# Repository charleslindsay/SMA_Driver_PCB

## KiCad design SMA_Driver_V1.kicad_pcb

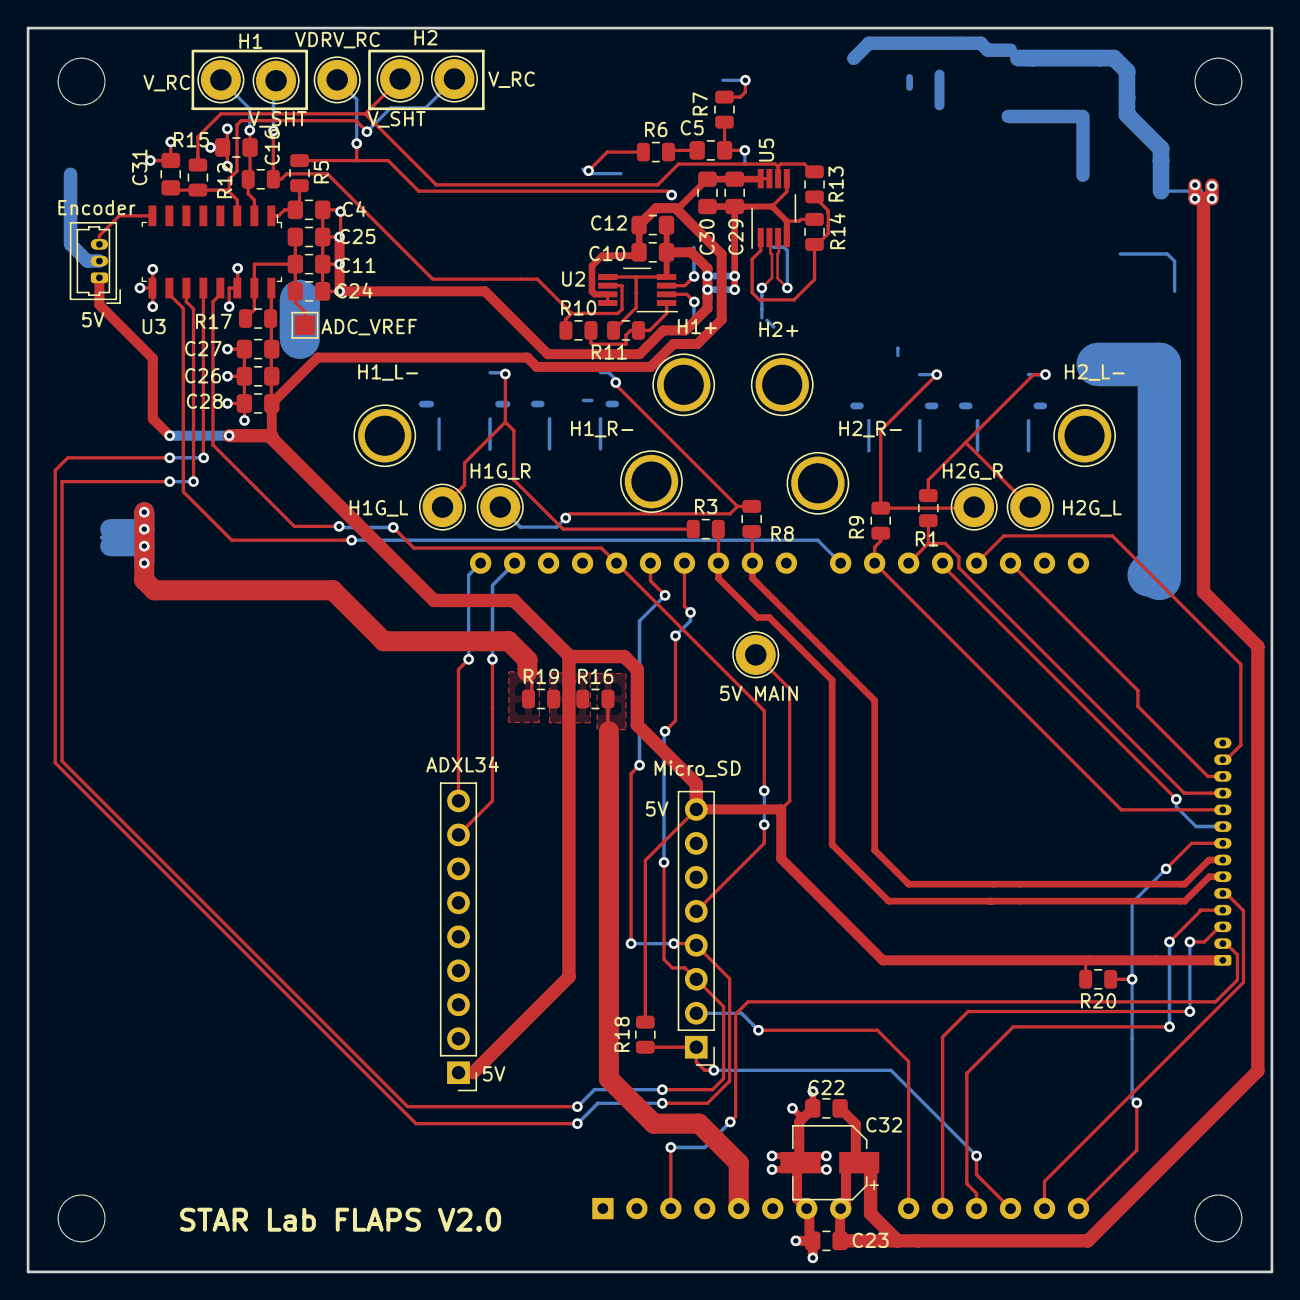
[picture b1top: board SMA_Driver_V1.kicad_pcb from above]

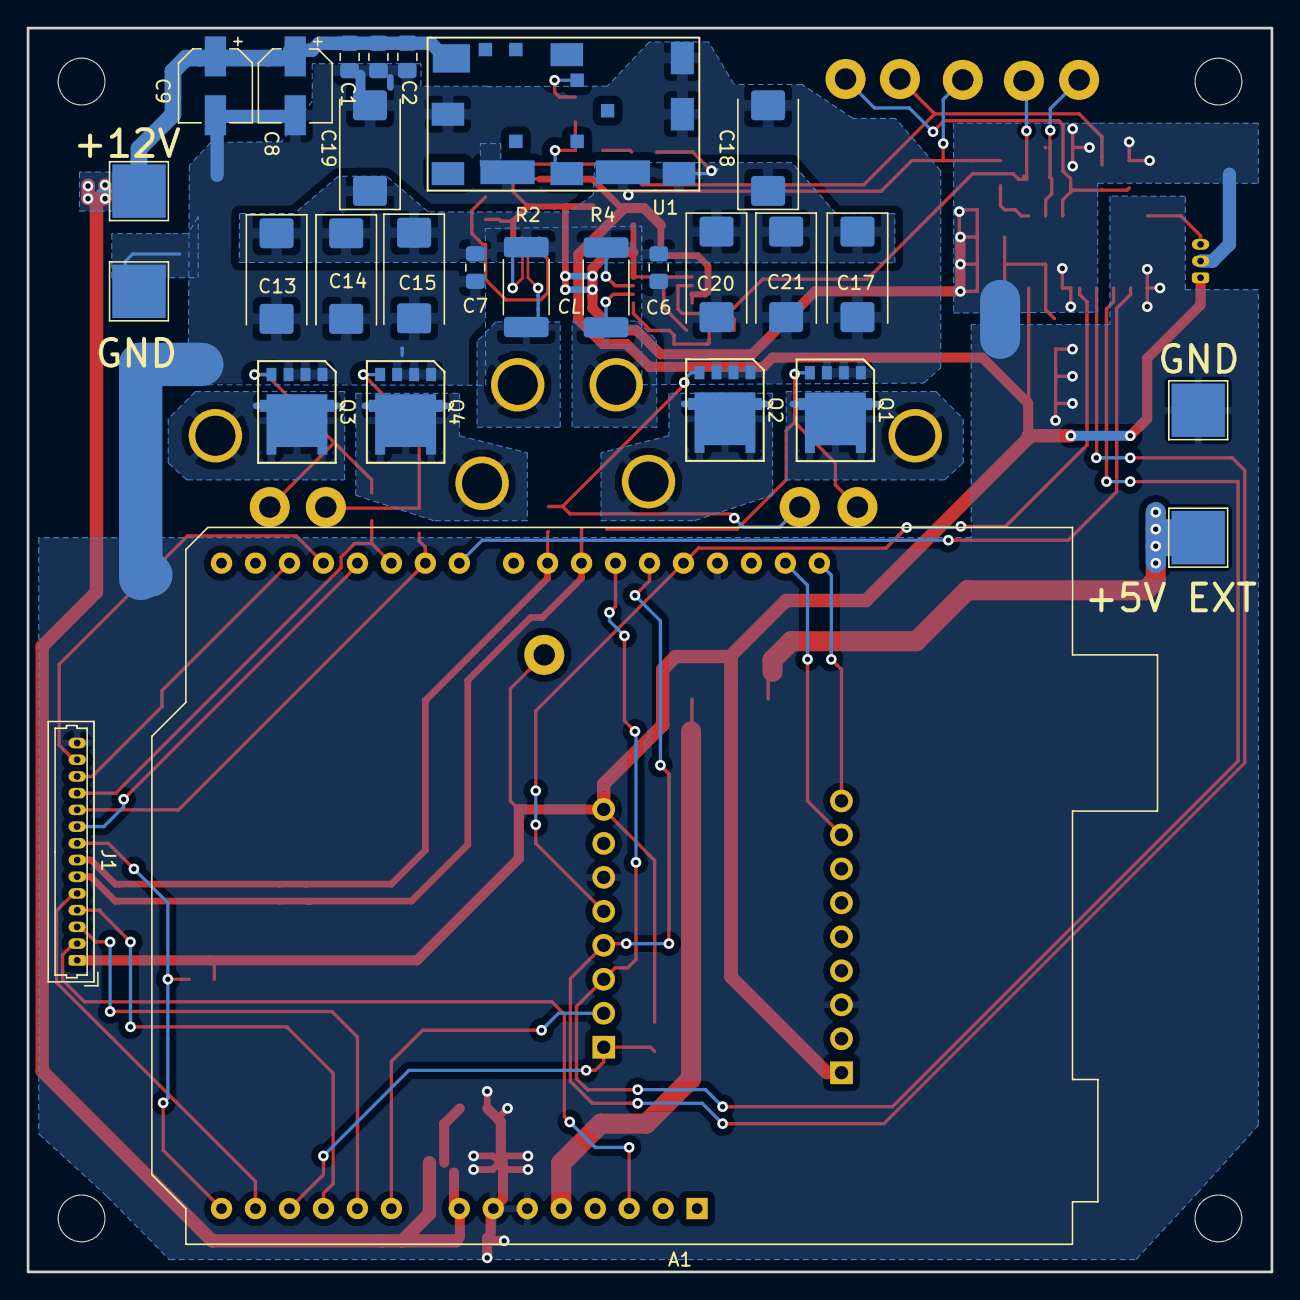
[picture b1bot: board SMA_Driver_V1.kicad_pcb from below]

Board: 2 copper layers, 93.0 x 93.0 mm, 86 parts (28 on the bottom side), 48 nets.

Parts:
A1: Arduino_UNO_R3
A2: ADXL34_Accelerometer; PinHeader_1x09_P2.54mm_Vertical
C1, C2, C3: 22uF; C_0805_2012Metric_Pad1.15x1.40mm_HandSolder
C4, C16, C31: 1uF; C_0805_2012Metric_Pad1.15x1.40mm_HandSolder
C5, C11, C28: 10n; C_0805_2012Metric_Pad1.15x1.40mm_HandSolder
C6, C7: 47uF; C_0805_2012Metric_Pad1.15x1.40mm_HandSolder
C8, C9, C32: 10uF; CP_Elec_5x5.3
C10, C23, C24, C27, C29: 100n; C_0805_2012Metric_Pad1.15x1.40mm_HandSolder
C12, C22, C25, C26, C30: 4.7u; C_0805_2012Metric_Pad1.15x1.40mm_HandSolder
C13, C14, C15, C17, C18, C19, C20, C21: 330u; CP_EIA-7343-43_Kemet-X_Pad2.25x2.55mm_HandSolder
J1: Human_Interface_Tether; Molex_PicoBlade_53047-2810_1x14_P1.25mm_Vertical
J2: RM08V_Conn; Molex_PicoBlade_53047-0610_1x03_P1.25mm_Vertical
Q1, Q2, Q3, Q4: Q_NMOS_GDS; SO-8FL_v2
R1, R3, R8, R9: 124; R_0805_2012Metric
R2, R4: 4m; R_2512_6332Metric_Pad1.52x3.35mm_HandSolder
R5, R7: 15.8k; R_0805_2012Metric
R6: 180; R_0805_2012Metric
R10, R13: 24k; R_0805_2012Metric
R11, R14: 1k; R_0805_2012Metric
R12, R15: 30k; R_0805_2012Metric
R16, R17, R19: 0; R_0805_2012Metric
R18, R20: 10k; R_0805_2012Metric
TP1: 12V_EXT; TestPoint_Pad_4.0x4.0mm
TP2, TP3: GND_EXT; TestPoint_Pad_4.0x4.0mm
TP4, TP17: Gate_1; TestPoint_Loop_D2.60mm_Drill1.6mm_Beaded
TP5: VDRV; TestPoint_Loop_D2.60mm_Drill1.6mm_Beaded
TP6, TP7: Gate_2; TestPoint_Loop_D2.60mm_Drill1.6mm_Beaded
TP8, TP15: SMA1-; TestPoint_Plated_Hole_D3.0mm
TP10: SMA2+; TestPoint_Plated_Hole_D3.0mm
TP11, TP18: SMA2-; TestPoint_Plated_Hole_D3.0mm
TP12: 5V_EXT; TestPoint_Pad_4.0x4.0mm
TP13: 5V; TestPoint_Loop_D2.60mm_Drill1.6mm_Beaded
TP14, TP20: I_SMA; TestPoint_Loop_D2.60mm_Drill1.6mm_Beaded
TP16: SMA1+; TestPoint_Plated_Hole_D3.0mm
TP19, TP21: I_SMA_LP; TestPoint_Loop_D2.60mm_Drill1.6mm_Beaded
TP22: VREF; TestPoint_Pad_1.5x1.5mm
U1: UDT020A0X3-SRZ
U2, U5: INA332; VSSOP-8_3.0x3.0mm_P0.65mm
U3: MCP3208; SOIC-16_W3.90mm
U4: MicroSD_Breakout_ADF; PinHeader_1x08_P2.54mm_Vertical

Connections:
+5V: A2.1, C10.1, C12.1, C26.1, C27.1, C28.1, C29.1, C30.1, J1.1, J2.1, R16.1, R17.1, R18.1, R19.2, R20.2, TP13.1, U2.7, U2.8, U3.16, U4.8, U5.7, U5.8
+5VP: R19.1, TP12.1
+12V: A1.8, C1.1, C2.1, C3.1, C8.1, C9.1, C22.1, C23.2, C32.1, TP1.1, U1.2
/5V_Arduino: A1.5, R16.2
/ADC_CS: A1.22, U3.10
/Accel_SCL: A1.32, A2.9
/Accel_SDA: A1.31, A2.8
/Button: A1.14, J1.8, R20.1
/Enc_Vout: J2.3, U3.8
/G_H1_L: Q1.1, R3.1, TP6.1
/G_H1_R: Q2.1, R8.2, TP4.1
/G_H2_L: Q3.1, R1.1, TP7.1
/G_H2_R: Q4.1, R9.2, TP17.1
/I_SEN1-: R4.2, TP16.1, U2.2
/I_SEN+: C6.1, C7.1, C13.1, C14.1, C15.1, C17.1, C18.1, C19.1, C20.1, C21.1, R2.1, R4.1, R5.2, R6.1, TP5.1, U1.6, U1.7, U2.3, U5.3
/I_SEN-: R2.2, TP10.1, U5.2
/I_SEN_Amp_1: R10.1, R12.2, TP14.1, U2.6
/I_SEN_Amp_2: R13.1, R15.2, TP20.1, U5.6
/LED_STAT_B1: A1.18, J1.13
/LED_STAT_B2: A1.19, J1.9
/LED_STAT_O: A1.13, J1.5
/LED_STAT_P: A1.17, J1.12
/MCU_RES: A1.3, J1.2
/POT_1: A1.10, J1.3
/POT_2: A1.11, J1.4
/SD_CD: A1.12, R18.2, U4.1
/SD_CS: A1.9, U4.2
/SMA_H1_L: A1.25, J1.6, R3.2
/SMA_H1_R: A1.24, J1.7, R8.1
/SMA_H2_L: A1.20, J1.11, R1.2
/SMA_H2_R: A1.21, J1.10, R9.1
/SPI_CLK: A1.28, U3.13, U4.5
/SPI_MISO: A1.27, U3.12, U4.4
/SPI_MOSI: A1.26, U3.11, U4.3
/VDRV_SEN: C4.1, R5.1, U3.1
/V_H1_L-: Q1.2, TP15.1
/V_H1_R-: Q2.2, TP18.1
/V_H2_L-: Q3.2, TP8.1
/V_H2_R-: Q4.2, TP11.1
/V_SHUNT_1: C16.1, R12.1, TP19.1, U3.2
/V_SHUNT_2: C31.1, R15.1, TP21.1, U3.3
/Vreg_TRIM: C5.2, R7.1, U1.5
GND: A1.6, A1.7, A1.29, A2.3, C1.2, C2.2, C3.2, C4.2, C6.2, C7.2, C8.2, C9.2, C10.2, C11.2, C12.2, C13.2, C14.2, C15.2, C16.2, C17.2, C18.2, C19.2, C20.2, C21.2, C22.2, C23.1, C24.2, C25.2, C26.2, C27.2, C28.2, C29.2, C30.2, C31.2, C32.2, J1.14, J2.2, Q1.3, Q2.3, Q3.3, Q4.3, R11.2, R14.2, TP2.1, TP3.1, U1.1, U1.4, U1.8, U1.10, U2.4, U2.5, U3.9, U3.14, U4.6, U5.4, U5.5
unnamed: C5.1, R6.2
unnamed: C11.1, C24.1, C25.1, R17.2, TP22.1, U3.15
unnamed: R7.2, U1.14
unnamed: R10.2, R11.1, U2.1
unnamed: R13.2, R14.1, U5.1

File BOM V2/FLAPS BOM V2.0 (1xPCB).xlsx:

| Quantity | Ref | Value | Order Link | Footprint | Component | Price per comp | Total Price
 | 2 | R2,R4 | 4m | https://www.digikey.com/product-detail/en/panasonic-electron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 | Resistor_SMD:R_2512_6332Metric_Pad1.52x3.35mm_HandSolder | Resistor
 |  | " | 6m | https://www.digikey.com/product-detail/en/panasonic-electron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
 | 4 | Q1,Q2,Q3,Q4 | Q_NMOS_GDS | https://www.digikey.com/product-detail/en/on-semiconductor/N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 | custom:SO-8FL_v2 | N-MOSFET transistor, gate/drain/source
 | 4 | R3,R8,R1,R9 | 125 | https://www.digikey.com/product-detail/en/yageo/RC0805FR-071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 | Resistor_SMD:R_0805_2012Metric | Resistor
 | 2 | U2 | INA332 | https://www.digikey.com/product-detail/en/texas-instruments/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 | Package_SO:VSSOP-8_3.0x3.0mm_P0.65mm
 | 1 | U1 | UDT020A0X3-SRZ | https://www.digikey.com/product-detail/en/ge-critical-power/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 | custom:UDT020A0X3-SRZ
 | 2 | R11,R14 | 1k | https://www.digikey.com/product-detail/en/rohm-semiconductor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 | Resistor_SMD:R_0805_2012Metric | Resistor
 | 2 | R10,R13 | 24k | https://www.digikey.com/product-detail/en/panasonic-electron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 | Resistor_SMD:R_0805_2012Metric | Resistor
 |  | " | 22k | https://www.digikey.com/product-detail/en/panasonic-electron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
 |  | " | 20k | https://www.digikey.com/product-detail/en/panasonic-electron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
 |  | " | 30k | https://www.digikey.com/product-detail/en/panasonic-electron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
 |  | " | 33k | https://www.digikey.com/product-detail/en/panasonic-electron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
 |  | " | 27k | https://www.digikey.com/product-detail/en/panasonic-electron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
 |  | " | 36k | https://www.digikey.com/product-detail/en/panasonic-electron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
 | 1 | R12 | 30k | https://www.digikey.com/product-detail/en/panasonic-electron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 | Resistor_SMD:R_0805_2012Metric | Resistor
 | 2 | C4,C16 | 1uF | https://www.digikey.com/product-detail/en/kemet/C0805C105J4R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 | Capacitor_SMD:C_0805_2012Metric_Pad1.15x1.40mm_HandSolder | Unpolarized capacitor
 | 2 | R5,R7 | 15.8k | https://www.digikey.com/product-detail/en/panasonic-electron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 | Resistor_SMD:R_0805_2012Metric | Resistor
 | 1 | U3 | MCP3208 | https://www.digikey.com/product-detail/en/microchip-technolo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 | digikey-footprints:SOIC-16_W3.90mm | A/D Converter, 12-Bit, 8-Channel, SPI Interface , 2.7V-5.5V
 | 3 | R16,R17,R19 | 0 | https://www.digikey.com/product-detail/en/vishay-dale/CRCW08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 | Resistor_SMD:R_0805_2012Metric | Resistor
 | 8 | C13-21 | 330u | https://www.digikey.com/product-detail/en/vishay-sprague/T55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 | Capacitor_Tantalum_SMD:CP_EIA-7343-43_Kemet-X_Pad2.25x2.55mm_HandSolder | Unpolarized capacitor
 | 2 | C6,C7 | 47uF | https://www.digikey.com/product-detail/en/samsung-electro-me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 | Capacitor_SMD:C_0805_2012Metric_Pad1.15x1.40mm_HandSolder | Unpolarized capacitor
 | 1 | R6 | 180 | https://www.digikey.com/product-detail/en/stackpole-electron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 | Resistor_SMD:R_0805_2012Metric | Resistor
 | 3 | C5,C11,C28 | 10n | https://www.digikey.com/product-detail/en/kemet/C0805C103K4R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 | Capacitor_SMD:C_0805_2012Metric_Pad1.15x1.40mm_HandSolder | Unpolarized capacitor
 | 3 | C1-3 | 22uF | https://www.digikey.com/product-detail/en/samsung-electro-me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 | Capacitor_SMD:C_0805_2012Metric_Pad1.15x1.40mm_HandSolder | Unpolarized capacitor
 | 4 | C10,C23,C24,C27 | 100n | https://www.digikey.com/product-detail/en/johanson-dielectri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 | Capacitor_SMD:C_0805_2012Metric_Pad1.15x1.40mm_HandSolder | Unpolarized capacitor
 | 3 | C12,C25,C26 | 4.7u | https://www.digikey.com/product-detail/en/samsung-electro-me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 | Capacitor_SMD:C_0805_2012Metric_Pad1.15x1.40mm_HandSolder | Unpolarized capacitor
 | 1 | A2 | ADXL34_Accelerometer | https://www.digikey.com/product-detail/en/adafruit-industrie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 | Connector_PinHeader_2.54mm:PinHeader_1x09_P2.54mm_Vertical
 | 1 | U4 | MicroSD_Breakout_ADF | https://www.digikey.com/products/en?mpart=254&v=1528 | Connector_PinHeader_2.54mm:PinHeader_1x08_P2.54mm_Vertical
 | 1 | R18 | 10k | https://www.digikey.com/product-detail/en/stackpole-electron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 | Resistor_SMD:R_0805_2012Metric | Resistor
 | 1 | J1 | Human_Interface_Tether | https://www.digikey.com/products/en/connectors-interconnects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 | Connector_Molex:Molex_PicoBlade_53047-2810_1x14_P1.25mm_Vertical | Generic connector, single row, 01x14, script generated (kicad-library-utils/sch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
 | 1 | J2 | RM08V_Conn | https://www.digikey.com/products/en/connectors-interconnects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 | Connector_Molex:Molex_PicoBlade_53047-0610_1x03_P1.25mm_Vertical | Generic connector, single row, 01x03, script generated (kicad-library-utils/sch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
 | 8 | TP6, TP4, TP14, TP19, TP7, TP17, TP20, TP21 | Gate_2 | https://www.digikey.com/product-detail/en/keystone-electroni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 | TestPoint:TestPoint_Loop_D2.60mm_Drill1.6mm_Beaded | test point
 | 3 | C8,C9,C32 | 10uF | https://www.digikey.com/product-detail/en/panasonic-electron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 | Capacitor_SMD:CP_Elec_5x5.3 | Unpolarized capacitor
 | 2 | C30,C22 | 4.7u | https://www.digikey.com/product-detail/en/samsung-electro-me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 | Capacitor_SMD:C_0805_2012Metric_Pad1.15x1.40mm_HandSolder | Unpolarized capacitor
 | 1 | NA | Tether Cable | https://www.digikey.com/product-detail/en/molex-llc/01513414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
 | 2 | NA | 8 pin header | https://www.digikey.com/products/en?keywords=Z5376-ND
 | 1 | NA | 10 pin header | https://www.digikey.com/products/en?keywords=732-2670-ND
 | 1 | NA | 6 pin header | https://www.digikey.com/products/en?keywords=732-5319-ND
 | 1 | NA | Encoder Cable | https://www.digikey.com/products/en/cable-assemblies/rectang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

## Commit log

2018-12-31 second commmit
2018-12-31 test
2018-12-31 undo test
2018-12-31 test branch
2019-01-01 fixed notes on 'SMA Driver V1 changes for V2'
2019-01-03 PCB Rev 2.0 Fixed issues on PCB changes for V2 doc
2019-01-07 added components for button, final draft 1
2019-01-07 Final Board V2.0 after run DMC check completed with no errors
2019-01-10 Final PCB version, sent to PCBWay for order on 1.10.19
2019-01-12 changed RC filter for Vin to have same resistor value as amp filter to eliminate common mode noise affecting comparison between Vin and Vshunt in code
2019-06-06 Misc Changes, and OMIT R20 to fix SDA tied to A4 issue
